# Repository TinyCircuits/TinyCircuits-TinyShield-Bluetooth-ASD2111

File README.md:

# TinyCircuits TinyShield Bluetooth Board
# ASD2111 Rev2

These are the design files for the TinyCircuits ASD2111 Rev 2 PCB.  This is a TinyShield board that has a Roving Networks RN42 Bluetooth 2.1 module, local power supply and level shifters to connect between the TinyDuino and the Bluetooth Module. 

Format is in Cadsoft Eagle format - Eagle version 6.2 was used for the original design.

For more infomation on this, check out the product page at Tiny-Circuits.com:  https://tiny-circuits.com/tiny-shield-bluetooth-163.html

#License:

Design by TinyCircuits.
All design files are released under the Creative Commons Attribution Share-Alike 3.0 License, see the following link for details: http://creativecommons.org/licenses/by-sa/3.0

All text above must be included in any redistribution or derived design

This project uses designs and concepts developed as part of the Arduino project and the LilyPad project.  The TinyCircuits design files themselves (schematics, PCB and libraries) are not directly derived from these works' design files and have been created new, however the concepts and basic architecture behind the TinyDuino and TinyLily products are derived and we thank the hard work of the organizations below for their contributions to open-source hardware:
  
Original Arduino Uno Design by Team Arduino

LilyPad Arduino Design by Leah Buechley and Sparkfun Electronics

Please support the open-source hardware community

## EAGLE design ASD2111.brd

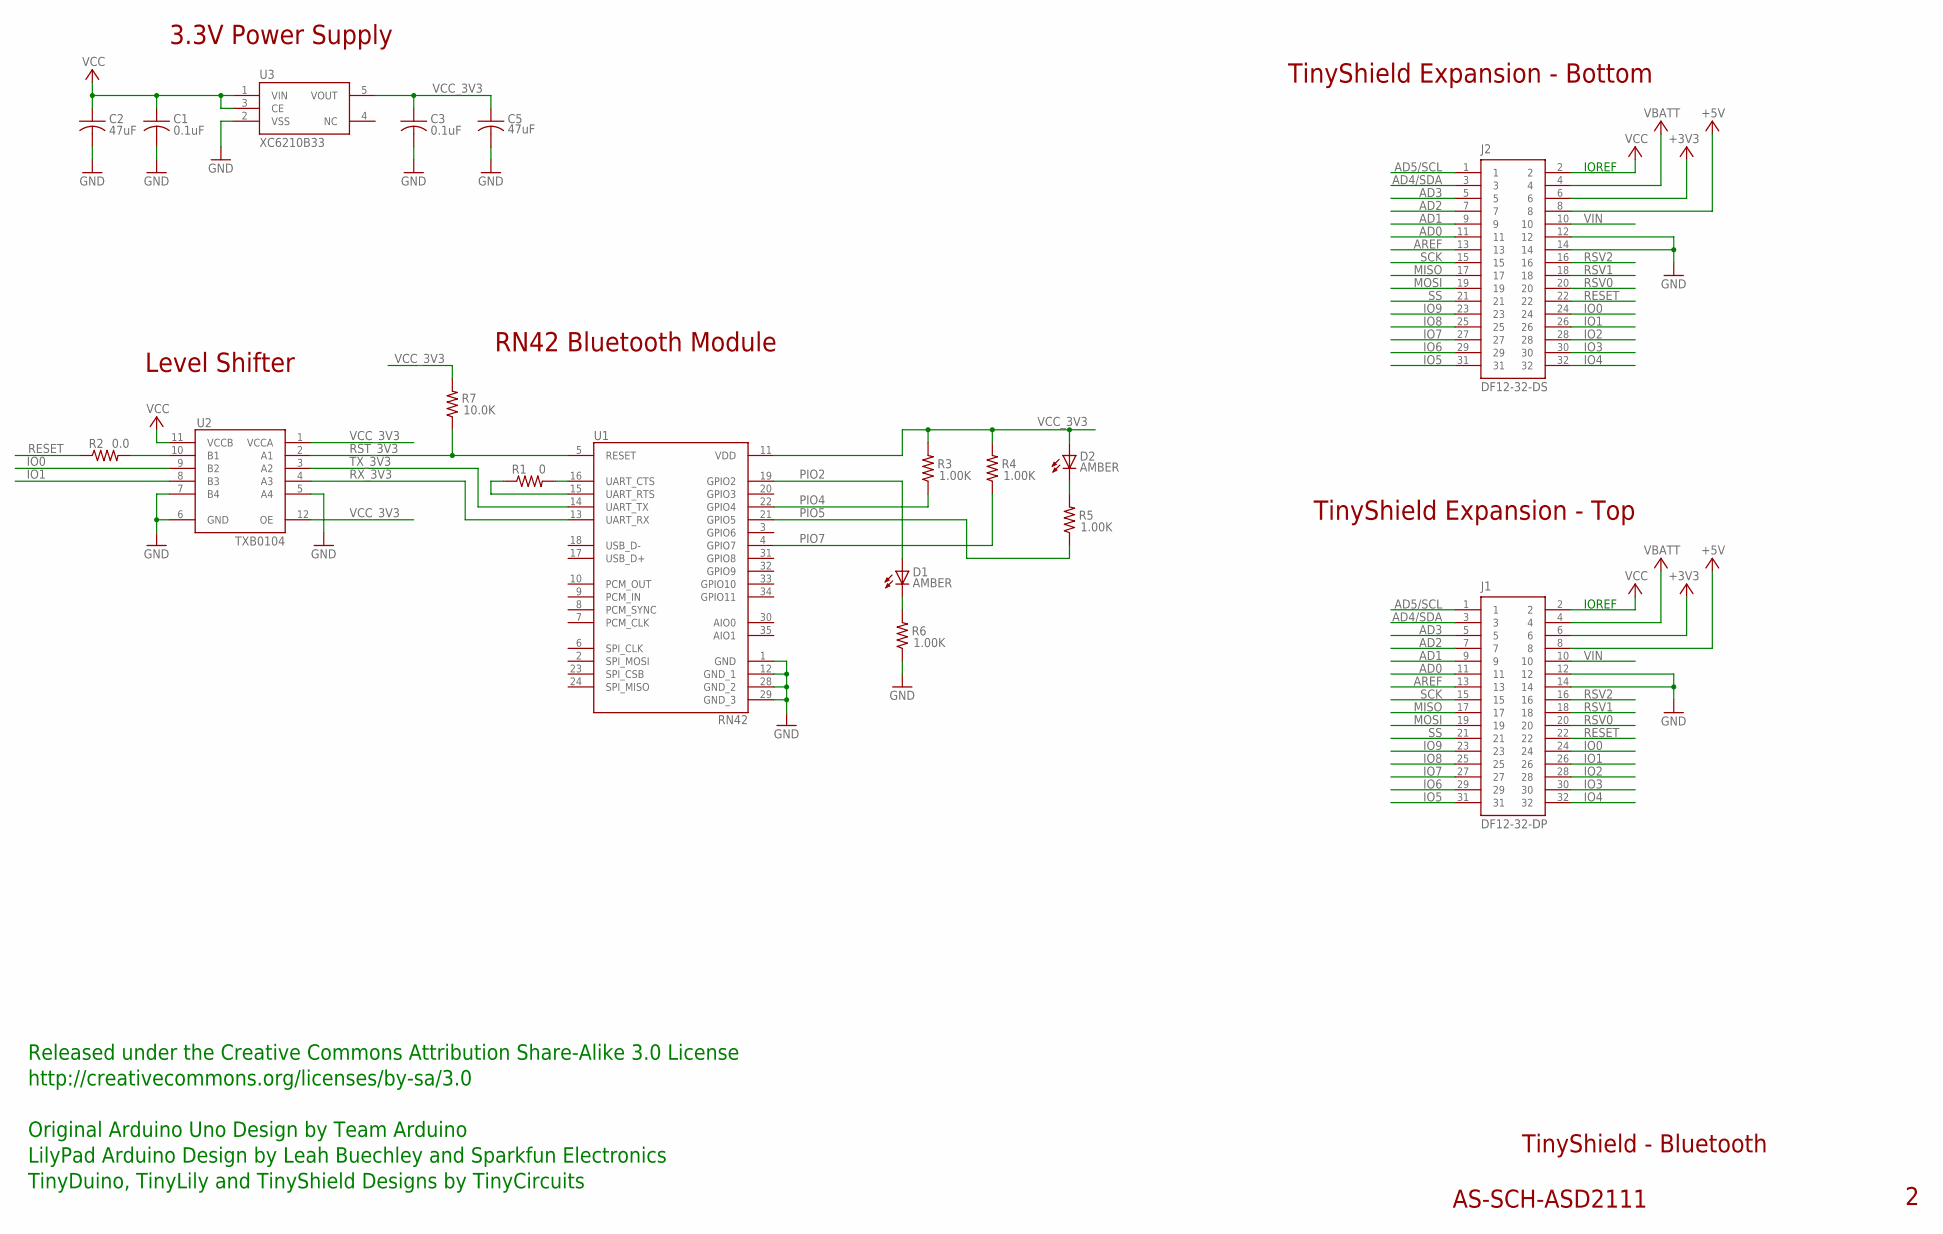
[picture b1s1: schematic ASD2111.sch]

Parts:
C1, C3: 0.1uF; C0402; PARTNO AS-ITM-00008
C2: 47uF; C1206; PARTNUM AS-ITM-00049
C5: 47uF; C1206
D1: AMBER; LNJ_LED
D2: AMBER; LNJ_LED; PARTNO AS-ITM-00026
J1: DF12-32-DP; PARTNO AS-ITM-00015
J2: DF12-32-DS; PARTNO AS-ITM-00012
R1: 0; 0402_SHORT
R2: 0.0; 0402
R3: 1.00K; 0402
R4, R5, R6: 1.00K; 0402; PARTNO AS-ITM-00003
R7: 10.0K; 0402
U1: RN42; RN42_BLUETOOTH_MODULE
U2: TXB0104; UQFN-12
U3: XC6210B33; SOT-25

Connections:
+3V3: J1.6, J2.6
+5V: J1.8, J2.8
AD0: J1.11, J2.11
AD1: J1.9, J2.9
AD2: J1.7, J2.7
AD3: J1.5, J2.5
AD4/SDA: J1.3, J2.3
AD5/SCL: J1.1, J2.1
AREF: J1.13, J2.13
GND: C1.2, C2.2, C3.2, C5.2, J1.12, J1.14, J2.12, J2.14, R6.1, U1.1 (GND), U1.12 (GND_1), U1.28 (GND_2), U1.29 (GND_3), U2.5 (A4), U2.6 (GND), U2.7 (B4), U3.2 (VSS)
IO0: J1.24, J2.24, U2.9 (B2)
IO1: J1.26, J2.26, U2.8 (B3)
IO2: J1.28, J2.28
IO3: J1.30, J2.30
IO4: J1.32, J2.32
IO5: J1.31, J2.31
IO6: J1.29, J2.29
IO7: J1.27, J2.27
IO8: J1.25, J2.25
IO9: J1.23, J2.23
MISO: J1.17, J2.17
MOSI: J1.19, J2.19
unnamed: R1.2, U1.16 (UART_CTS)
unnamed: R1.1, U1.15 (UART_RTS)
unnamed: R2.2, U2.10 (B1)
unnamed: D1.C, R6.2
unnamed: D2.C, R5.2
PIO2: D1.A, U1.19 (GPIO2)
PIO4: R3.1, U1.22 (GPIO4)
PIO5: R5.1, U1.21 (GPIO5)
PIO7: R4.1, U1.4 (GPIO7)
RESET: J1.22, J2.22, R2.1
RST_3V3: R7.1, U1.5 (RESET), U2.2 (A1)
RSV0: J1.20, J2.20
RSV1: J1.18, J2.18
RSV2: J1.16, J2.16
RX_3V3: U1.13 (UART_RX), U2.4 (A3)
SCK: J1.15, J2.15
SS: J1.21, J2.21
TX_3V3: U1.14 (UART_TX), U2.3 (A2)
VBATT: J1.4, J2.4
VCC: C1.1, C2.1, J1.2, J2.2, U2.11 (VCCB), U3.1 (VIN), U3.3 (CE)
VCC_3V3: C3.1, C5.1, D2.A, R3.2, R4.2, R7.2, U1.11 (VDD), U2.1 (VCCA), U2.12 (OE), U3.5 (VOUT)
VIN: J1.10, J2.10

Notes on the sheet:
TinyShield Expansion - Bottom
TinyShield - Bluetooth
AS-SCH-ASD2111
TinyShield Expansion - Top
IOREF
Released under the Creative Commons Attribution Share-Alike 3.0 License
http://creativecommons.org/licenses/by-sa/3.0
LilyPad Arduino Design by Leah Buechley and Sparkfun Electronics
TinyDuino, TinyLily and TinyShield Designs by TinyCircuits
Original Arduino Uno Design by Team Arduino
3.3V Power Supply
RN42 Bluetooth Module
Level Shifter

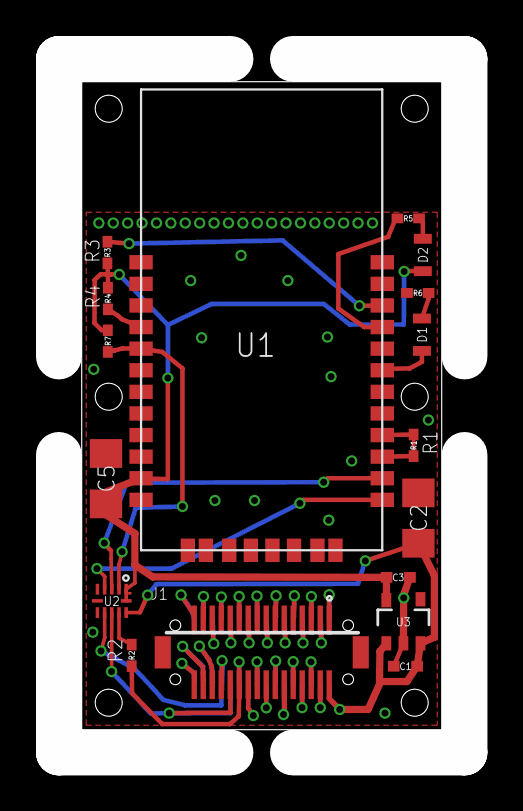
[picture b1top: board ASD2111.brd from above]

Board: 2 copper layers, 20.0 x 36.0 mm, 19 parts (1 on the bottom side), 44 nets.

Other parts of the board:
U$1: DOCFIELD-TINYCIRCUITS-PCB

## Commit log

2014-08-24 Updated Link
